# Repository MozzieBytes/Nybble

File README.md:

# Nybble
Cherry MX, and Alps compatible 45-key mechanical keyboard

## Features:
  - QMK compatible ATMEGA32u4 microcontroller.
  - Per-key diodes for n-key rollover support.
  - Alps, and Cherry MX compatible switch footprints to allow for a wide range of supported switch types.
  
## TODO:
  - Add LED support to the pcb.
  - Budget-oriented option for PCB to allow use of Teensy 2.0 microcontroller to reduce costs of pcb production.
  - Add SVG files for laser-cut sandwich case.
  - Create default QMK Firmware configuration for plug-and-play functionality.
  - Add silkscreening to pcb

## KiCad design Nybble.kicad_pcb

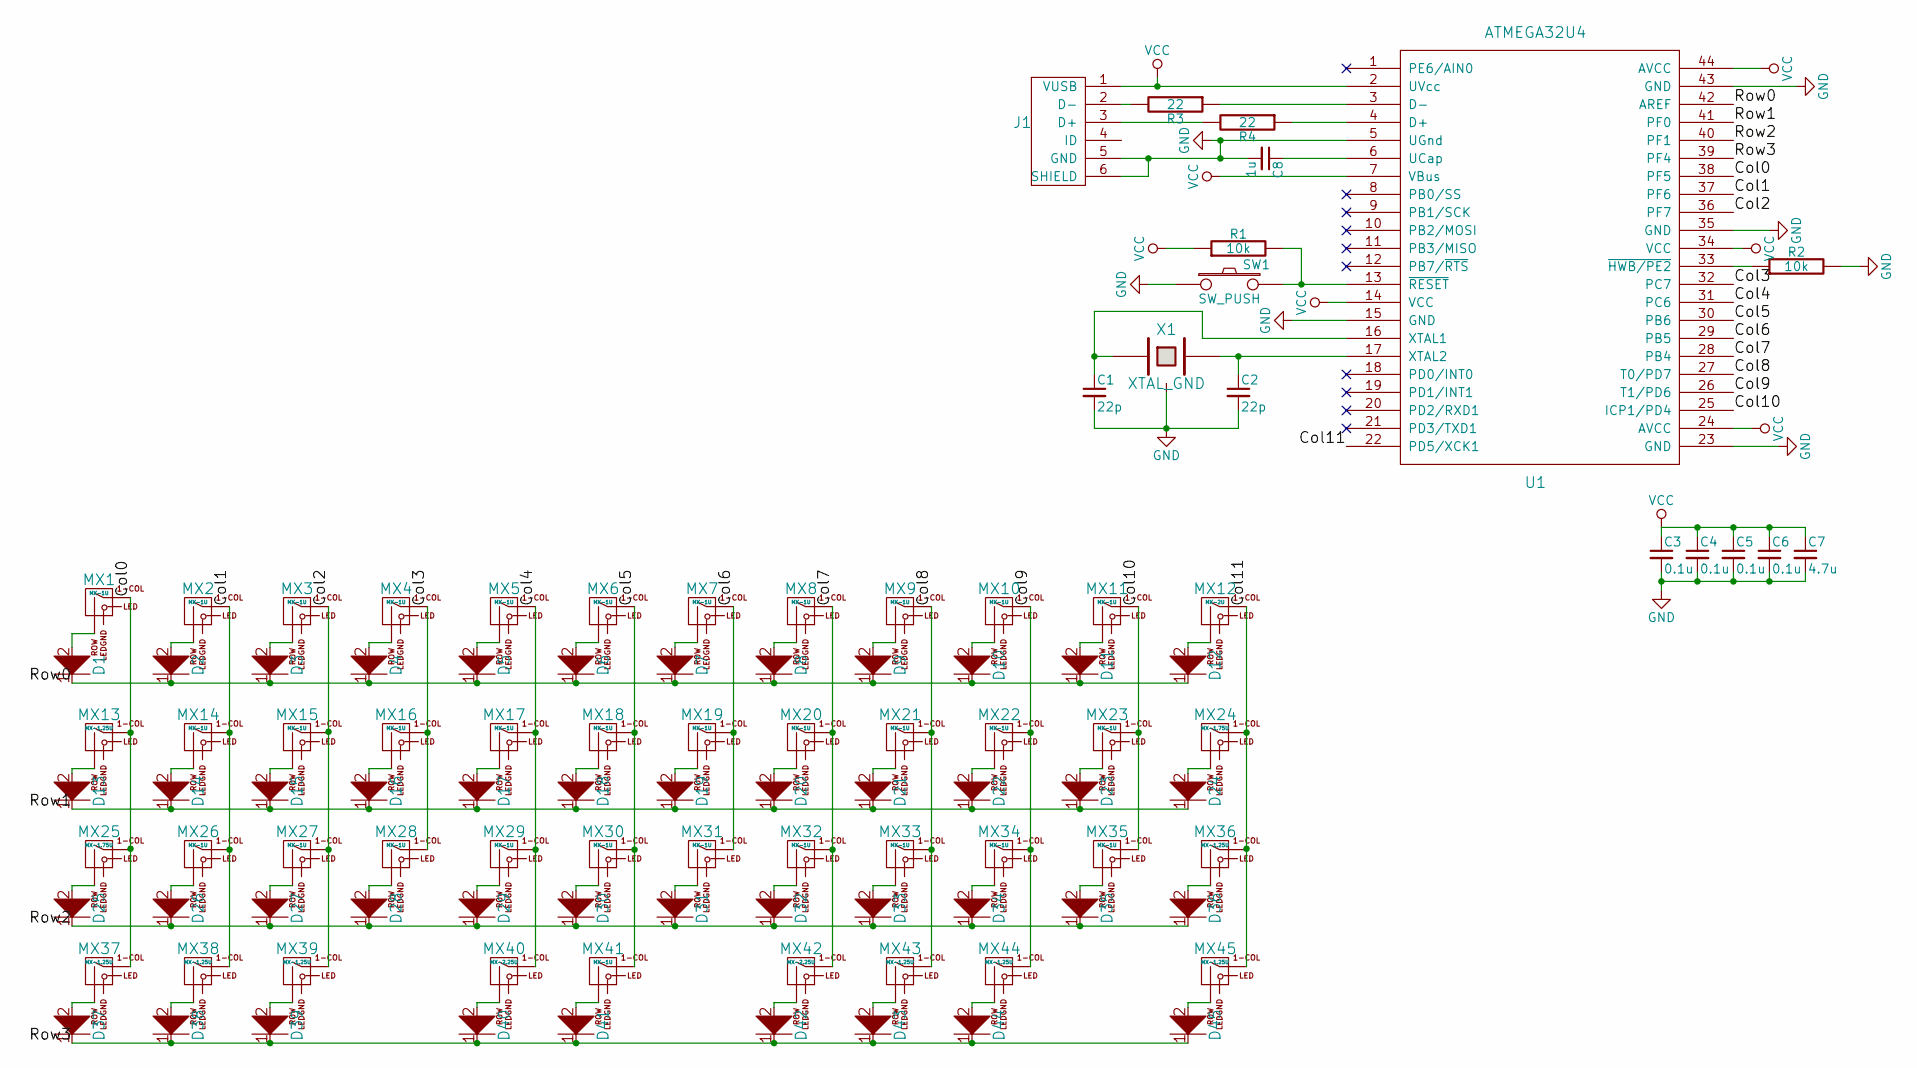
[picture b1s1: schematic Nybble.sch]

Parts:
C1, C2: 22p; C_0805_HandSoldering
C3, C4, C5, C6: 0.1u; C_0805_HandSoldering
C7: 4.7u; C_0805_HandSoldering
C8: 1u; C_0805_HandSoldering
D1, D2, D3, D4, D5, D6, D7, D8, D9, D10, D11, D12, D13, D14, D15, D16, D17, D18, D19, D20, D21, D22, D23, D24, D25, D26, D27, D28, D29, D30, D31, D32, D33, D34, D35, D36, D37, D38, D39, D40, D41, D42, D43, D44, D45: D; D_SOD123_axial
J1: USB_mini_micro_B; USB_miniB_hirose_5S8
MX1, MX2, MX3, MX4, MX5, MX6, MX7, MX8, MX9, MX10, MX11, MX14, MX15, MX16, MX17, MX18, MX19, MX20, MX21, MX22, MX23, MX26, MX27, MX28, MX29, MX30, MX31, MX32, MX33, MX34, MX35, MX41: MX-1U; MX-1U-NoLED
MX12: MX-2U; MX-2U-NoLED
MX13, MX36, MX37, MX38, MX39, MX43, MX44, MX45: MX-1.25U; MX-1.25U-NoLED
MX24, MX25: MX-1.75U; MX-1.75U-NoLED
MX40, MX42: MX-2.25U; MX-2.25U-NoLED
R1, R2: 10k; R_0805_HandSoldering
R3, R4: 22; R_0805_HandSoldering
SW1: SW_PUSH; SW_SPST_TL3342
U1: ATMEGA32U4; TQFP-44_10x10mm_Pitch0.8mm
X1: XTAL_GND; Crystal_SMD_3225-4pin_3.2x2.5mm

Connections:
/Col0: MX1.1 (COL), MX13.1 (COL), MX25.1 (COL), MX37.1 (COL), U1.38 (PF5)
/Col1: MX2.1 (COL), MX14.1 (COL), MX26.1 (COL), MX38.1 (COL), U1.37 (PF6)
/Col2: MX3.1 (COL), MX15.1 (COL), MX27.1 (COL), MX39.1 (COL), U1.36 (PF7)
/Col3: MX4.1 (COL), MX16.1 (COL), MX28.1 (COL), U1.32 (PC7)
/Col4: MX5.1 (COL), MX17.1 (COL), MX29.1 (COL), MX40.1 (COL), U1.31 (PC6)
/Col5: MX6.1 (COL), MX18.1 (COL), MX30.1 (COL), MX41.1 (COL), U1.30 (PB6)
/Col6: MX7.1 (COL), MX19.1 (COL), MX31.1 (COL), U1.29 (PB5)
/Col7: MX8.1 (COL), MX20.1 (COL), MX32.1 (COL), MX42.1 (COL), U1.28 (PB4)
/Col8: MX9.1 (COL), MX21.1 (COL), MX33.1 (COL), MX43.1 (COL), U1.27 (T0/PD7)
/Col9: MX10.1 (COL), MX22.1 (COL), MX34.1 (COL), MX44.1 (COL), U1.26 (T1/PD6)
/Col10: MX11.1 (COL), MX23.1 (COL), MX35.1 (COL), U1.25 (ICP1/PD4)
/Col11: MX12.1 (COL), MX24.1 (COL), MX36.1 (COL), MX45.1 (COL), U1.22 (PD5/XCK1)
/Row0: D1.1, D2.1, D3.1, D4.1, D5.1, D6.1, D7.1, D8.1, D9.1, D10.1, D11.1, D12.1, U1.42 (AREF)
/Row1: D13.1, D14.1, D15.1, D16.1, D17.1, D18.1, D19.1, D20.1, D21.1, D22.1, D23.1, D24.1, U1.41 (PF0)
/Row2: D25.1, D26.1, D27.1, D28.1, D29.1, D30.1, D31.1, D32.1, D33.1, D34.1, D35.1, D36.1, U1.40 (PF1)
/Row3: D37.1, D38.1, D39.1, D40.1, D41.1, D42.1, D43.1, D44.1, D45.1, U1.39 (PF4)
GND: C1.2, C2.2, C3.2, C4.2, C5.2, C6.2, C7.2, C8.2, J1.5 (GND), J1.6 (SHIELD), R2.2, SW1.1, U1.5 (UGnd), U1.15 (GND), U1.23 (GND), U1.35 (GND), U1.43 (GND), X1.3
unnamed: C1.1, U1.16 (XTAL1), X1.1
unnamed: C2.1, U1.17 (XTAL2), X1.2
unnamed: C8.1, U1.6 (UCap)
unnamed: D1.2, MX1.2 (ROW)
unnamed: D2.2, MX2.2 (ROW)
unnamed: D3.2, MX3.2 (ROW)
unnamed: D4.2, MX4.2 (ROW)
unnamed: D5.2, MX5.2 (ROW)
unnamed: D6.2, MX6.2 (ROW)
unnamed: D7.2, MX7.2 (ROW)
unnamed: D8.2, MX8.2 (ROW)
unnamed: D9.2, MX9.2 (ROW)
unnamed: D10.2, MX10.2 (ROW)
unnamed: D11.2, MX11.2 (ROW)
unnamed: D12.2, MX12.2 (ROW)
unnamed: D13.2, MX13.2 (ROW)
unnamed: D14.2, MX14.2 (ROW)
unnamed: D15.2, MX15.2 (ROW)
unnamed: D16.2, MX16.2 (ROW)
unnamed: D17.2, MX17.2 (ROW)
unnamed: D18.2, MX18.2 (ROW)
unnamed: D19.2, MX19.2 (ROW)
unnamed: D20.2, MX20.2 (ROW)
unnamed: D21.2, MX21.2 (ROW)
unnamed: D22.2, MX22.2 (ROW)
unnamed: D23.2, MX23.2 (ROW)
unnamed: D24.2, MX24.2 (ROW)
unnamed: D25.2, MX25.2 (ROW)
unnamed: D26.2, MX26.2 (ROW)
unnamed: D27.2, MX27.2 (ROW)
unnamed: D28.2, MX28.2 (ROW)
unnamed: D29.2, MX29.2 (ROW)
unnamed: D30.2, MX30.2 (ROW)
unnamed: D31.2, MX31.2 (ROW)
unnamed: D32.2, MX32.2 (ROW)
unnamed: D33.2, MX33.2 (ROW)
unnamed: D34.2, MX34.2 (ROW)
unnamed: D35.2, MX35.2 (ROW)
unnamed: D36.2, MX36.2 (ROW)
unnamed: D37.2, MX37.2 (ROW)
unnamed: D38.2, MX38.2 (ROW)
unnamed: D39.2, MX39.2 (ROW)
unnamed: D40.2, MX40.2 (ROW)
unnamed: D41.2, MX41.2 (ROW)
unnamed: D42.2, MX42.2 (ROW)
unnamed: D43.2, MX43.2 (ROW)
unnamed: D44.2, MX44.2 (ROW)
unnamed: D45.2, MX45.2 (ROW)
unnamed: J1.2 (D-), R3.2
unnamed: J1.3 (D+), R4.2
unnamed: R1.2, SW1.2, U1.13 (~RESET)
unnamed: R2.1, U1.33 (~HWB/PE2)
unnamed: R3.1, U1.3 (D-)
unnamed: R4.1, U1.4 (D+)
VCC: C3.1, C4.1, C5.1, C6.1, C7.1, J1.1 (VUSB), R1.1, U1.2 (UVcc), U1.7 (VBus), U1.14 (VCC), U1.24 (AVCC), U1.34 (VCC), U1.44 (AVCC)

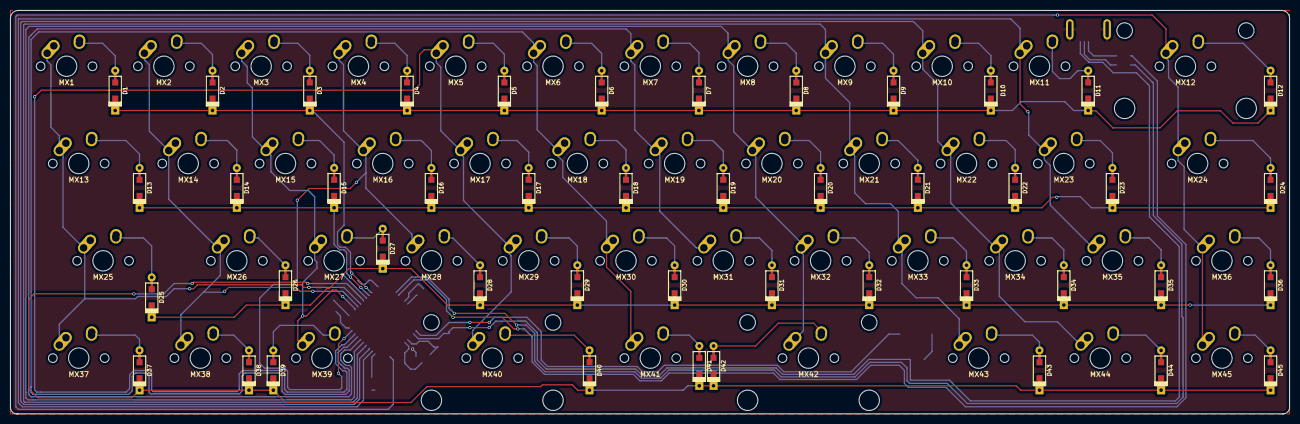
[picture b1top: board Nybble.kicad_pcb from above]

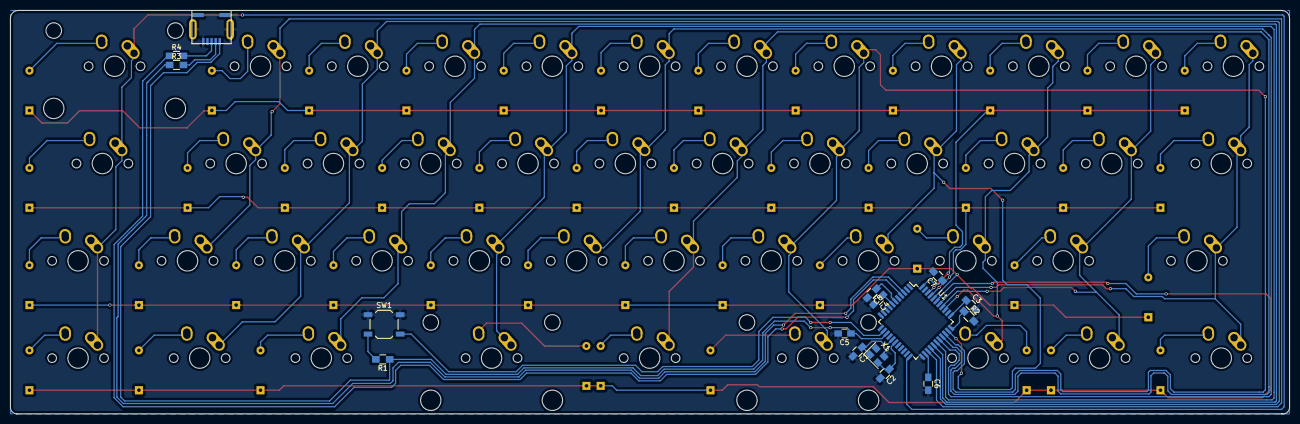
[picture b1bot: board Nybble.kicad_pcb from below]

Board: 2 copper layers, 250.4 x 79.0 mm, 106 parts (16 on the bottom side), 72 nets.

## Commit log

2018-01-26 Implemented gitignore from https://github.com/github/gitignore/blob/master/KiCad.gitignore
2018-01-26 Initial Commit, half completed PCB
2018-01-26 Added empty README
2018-01-26 Finished the Switch Matrix -- May need to fix the labels
2018-01-28 I screwed with a tonne of footprints, and attempted to generate a netlist, currently untested
2018-01-28 Fixed issues in row connection
2018-01-28 Moving all the controller smd components around the pcb
2018-01-28 Got a draft of the component layout
2018-01-28 Made a few fine edits to the controller
2018-01-28 Created PCB edge
2018-01-28 Added Ground zones
2018-01-28 Filled Ground Zones
2018-01-28 Fixed issues with the diode on switch 27
2018-01-28 Starting to add traces to keyboard
2018-01-29 Fixed reset switch, and added a via between the two ground planes
2018-01-29 Fixed issues with the schematic
2018-01-29 Finished the traces between the switches and the diodes
2018-01-29 Finished Wiring COlumns
2018-01-29 Finished routing the connections for the rows
2018-01-29 Fixed issues with row, and column traces
2018-01-29 Fixed issues with the netlist
2018-01-29 Wired up the rows for the pcb
2018-01-29 Routed all columnar traces
2018-01-29 Started rerouting everything on the pcb. I made so many silly mistakes
2018-01-29 Just about to leave class
2018-01-30 5 traces to go
2018-01-30 Finished pcb traces
2018-02-05 Fixed a few traces that were breaking the ground plane
2018-02-05 Fixed the traces by switch 37
